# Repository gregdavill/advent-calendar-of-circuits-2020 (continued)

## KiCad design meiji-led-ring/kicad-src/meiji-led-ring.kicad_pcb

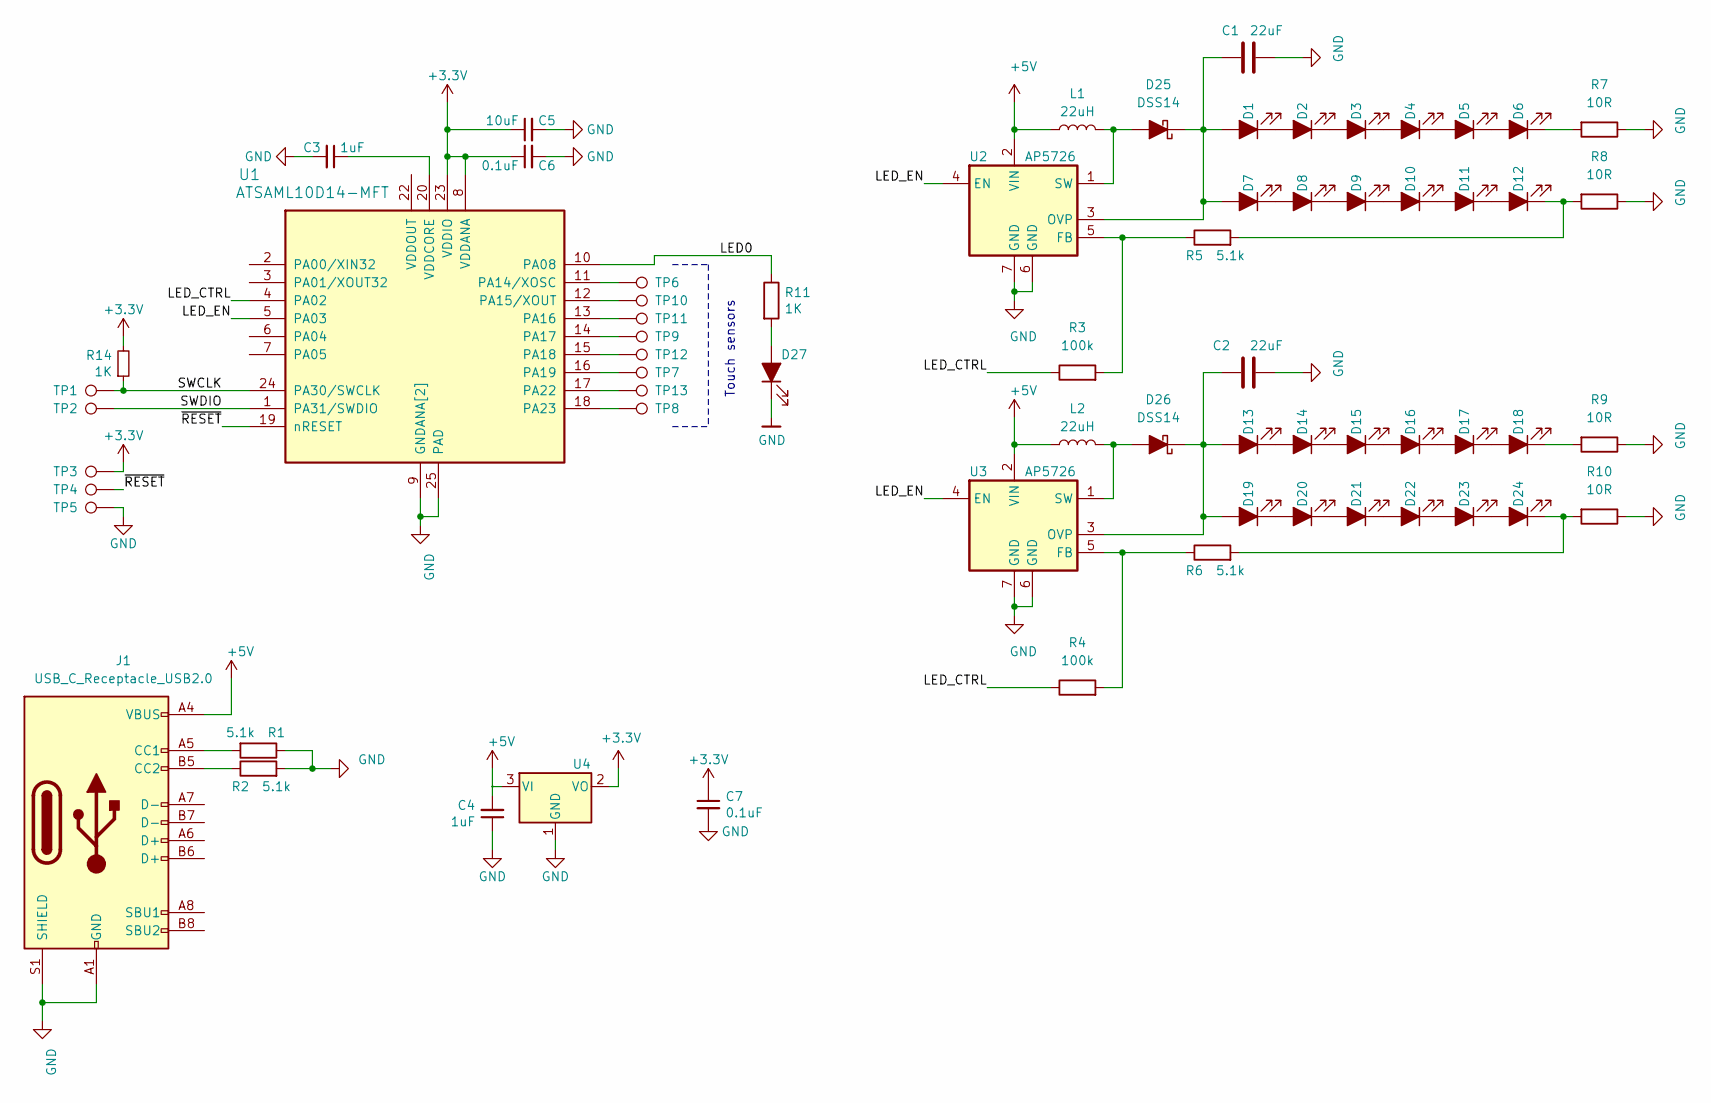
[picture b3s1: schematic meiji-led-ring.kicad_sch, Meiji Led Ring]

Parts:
C1, C2: 22uF; C_1210_3225Metric
C3, C4: 1uF; C_0402_1005Metric
C5: 10uF; C_0402_1005Metric
C6, C7: 0.1uF; C_0402_1005Metric
D1, D2, D3, D4, D5, D6, D7, D8, D9, D10, D11, D12, D13, D14, D15, D16, D17, D18, D19, D20, D21, D22, D23, D24: LED_ALT; LED_LUXEON_3014
D25, D26: DSS14; D_SOD-123F
D27: LED_ALT; LED_0402_1005Metric
J1: USB_C_Receptacle_USB2.0; USB_C_Receptacle_HRO_TYPE-C-31-M-12
L1, L2: 22uH; L_Taiyo-Yuden_NR-40xx
R1, R2, R5, R6: 5.1k; R_0402_1005Metric
R3, R4: 100k; R_0402_1005Metric
R7, R8, R9, R10: 10R; R_0603_1608Metric
R11, R14: 1K; R_0402_1005Metric
TP1: TP_SWCLK; TestPoint_Pad_D1.0mm
TP2: TP_SWDIO; TestPoint_Pad_D1.0mm
TP3: TP_VDD; TestPoint_Pad_D1.0mm
TP4: TP_RESET; TestPoint_Pad_D1.0mm
TP5: TP_GND; TestPoint_Pad_D1.0mm
TP6, TP7, TP8, TP9, TP10, TP11, TP12, TP13: TP_SWCLK; touch_edge_arc
U1: ATSAML10D14-MFT; QFN-24-1EP_5x5mm_P0.65mm_EP3.4x3.4mm
U2, U3: AP5726; DFN-6-1EP_2x2mm_P0.65mm_EP1x1.6mm
U4: MCP1700-3302E_SOT23; SOT-23

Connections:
+3V3: C5.1, C6.1, C7.1, R14.2, TP3.1, U1.8 (VDDANA), U1.23 (VDDIO), U4.2 (VO)
+5V: C4.2, J1.A4 (VBUS), J1.A9 (VBUS), J1.B4 (VBUS), J1.B9 (VBUS), L1.1, L2.1, U2.2 (VIN), U3.2 (VIN), U4.3 (VI)
/LED0: R11.1, U1.10 (PA08)
/LED_CTRL: R3.1, R4.1, U1.4 (PA02)
/LED_EN: U1.5 (PA03), U2.4 (EN), U3.4 (EN)
/SWCLK: R14.1, TP1.1, U1.24 (PA30/SWCLK)
/SWDIO: TP2.1, U1.1 (PA31/SWDIO)
/~RESET~: TP4.1, U1.19 (nRESET)
GND: C1.2, C2.2, C3.2, C4.1, C5.2, C6.2, C7.2, D27.1 (K), J1.A1 (GND), J1.A12 (GND), J1.B1 (GND), J1.B12 (GND), J1.S1 (SHIELD), R1.1, R2.2, R7.1, R8.1, R9.1, R10.1, TP5.1, U1.9 (GNDANA[2]), U1.21 (GNDANA[2]), U1.25 (PAD), U2.6 (GND), U2.7 (GND), U3.6 (GND), U3.7 (GND), U4.1 (GND)
unnamed: C1.1, D1.2 (A), D7.2 (A), D25.1 (K), U2.3 (OVP)
unnamed: C2.1, D13.2 (A), D19.2 (A), D26.1 (K), U3.3 (OVP)
unnamed: C3.1, U1.20 (VDDCORE)
unnamed: D1.1 (K), D2.2 (A)
unnamed: D2.1 (K), D3.2 (A)
unnamed: D3.1 (K), D4.2 (A)
unnamed: D4.1 (K), D5.2 (A)
unnamed: D5.1 (K), D6.2 (A)
unnamed: D6.1 (K), R7.2
unnamed: D7.1 (K), D8.2 (A)
unnamed: D8.1 (K), D9.2 (A)
unnamed: D10.1 (K), D11.2 (A)
unnamed: D9.1 (K), D10.2 (A)
unnamed: D11.1 (K), D12.2 (A)
unnamed: D12.1 (K), R5.2, R8.2
unnamed: D13.1 (K), D14.2 (A)
unnamed: D14.1 (K), D15.2 (A)
unnamed: D15.1 (K), D16.2 (A)
unnamed: D16.1 (K), D17.2 (A)
unnamed: D17.1 (K), D18.2 (A)
unnamed: D18.1 (K), R9.2
unnamed: D19.1 (K), D20.2 (A)
unnamed: D20.1 (K), D21.2 (A)
unnamed: D21.1 (K), D22.2 (A)
unnamed: D22.1 (K), D23.2 (A)
unnamed: D23.1 (K), D24.2 (A)
unnamed: D24.1 (K), R6.2, R10.2
unnamed: D25.2 (A), L1.2, U2.1 (SW)
unnamed: D26.2 (A), L2.2, U3.1 (SW)
unnamed: D27.2 (A), R11.2
unnamed: J1.A5 (CC1), R1.2
unnamed: J1.B5 (CC2), R2.1
unnamed: R3.2, R5.1, U2.5 (FB)
unnamed: R4.2, R6.1, U3.5 (FB)
unnamed: TP6.1, U1.11 (PA14/XOSC)
unnamed: TP7.1, U1.16 (PA19)
unnamed: TP8.1, U1.18 (PA23)
unnamed: TP9.1, U1.14 (PA17)
unnamed: TP10.1, U1.12 (PA15/XOUT)
unnamed: TP11.1, U1.13 (PA16)
unnamed: TP12.1, U1.15 (PA18)
unnamed: TP13.1, U1.17 (PA22)

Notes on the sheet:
Touch sensors

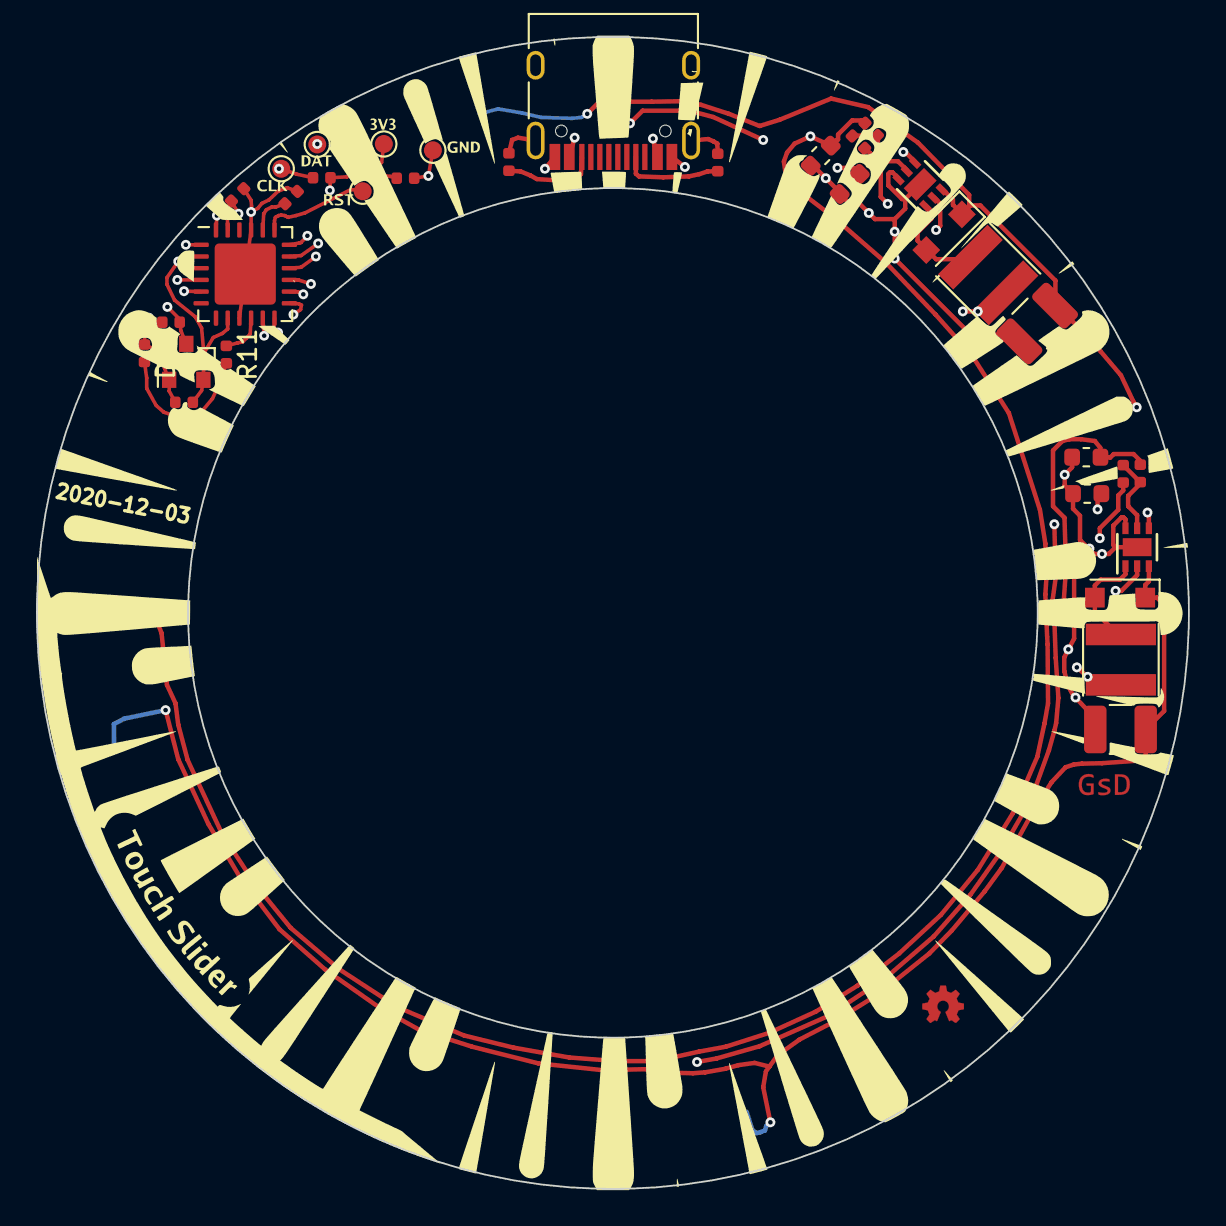
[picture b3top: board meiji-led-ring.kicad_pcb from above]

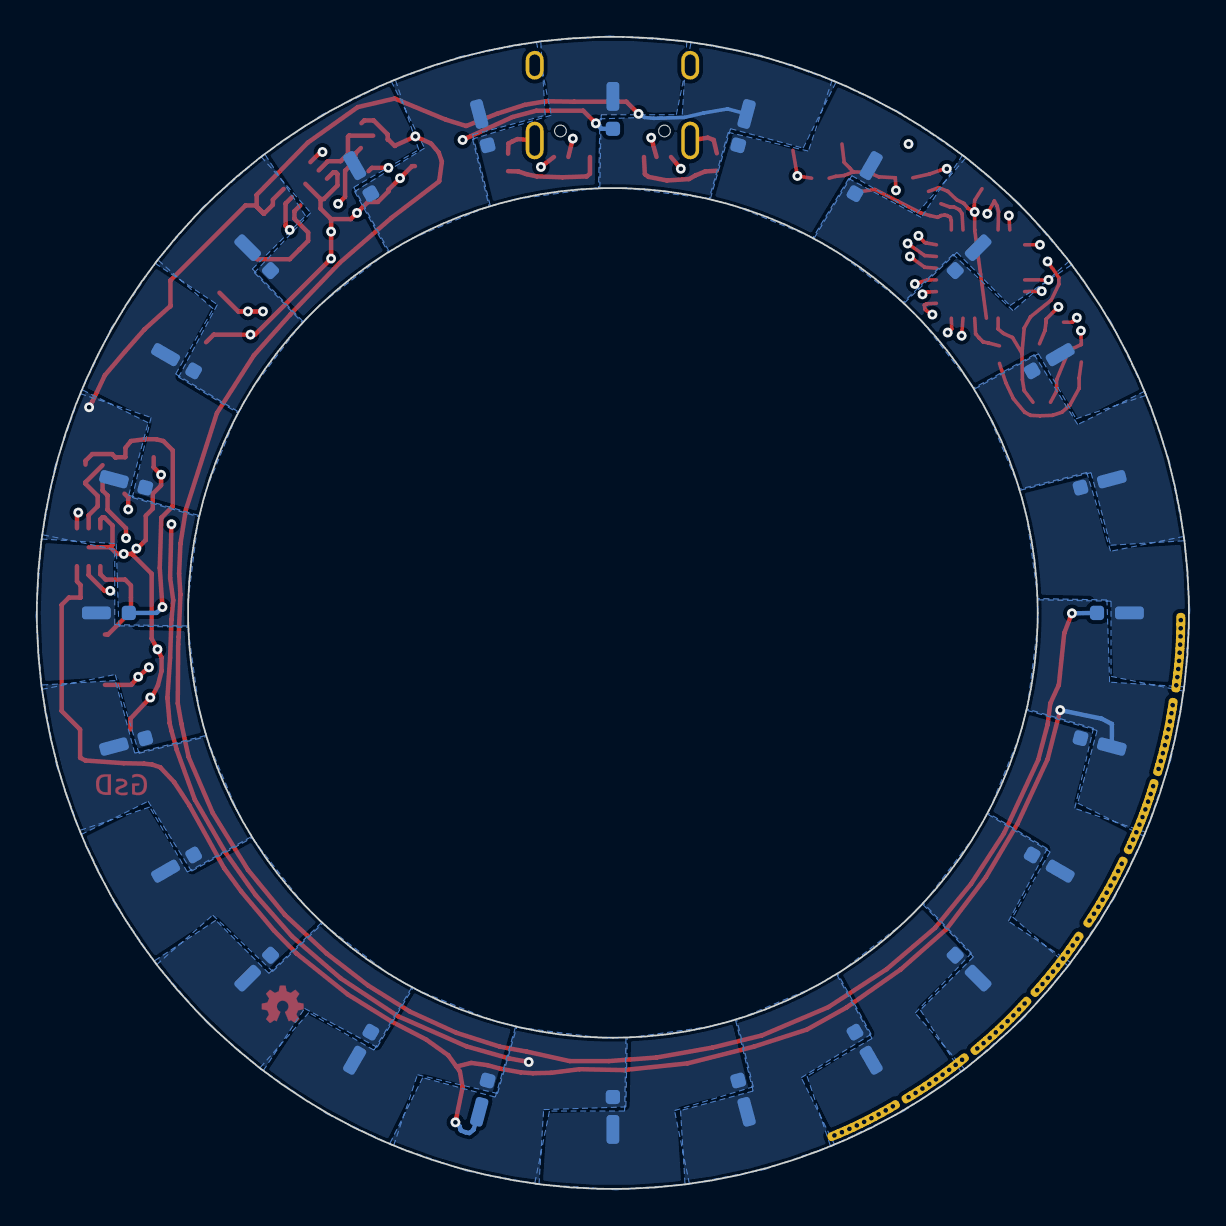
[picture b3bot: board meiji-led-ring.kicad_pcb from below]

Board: 4 copper layers, 64.0 x 64.0 mm, 66 parts (24 on the bottom side), 51 nets.

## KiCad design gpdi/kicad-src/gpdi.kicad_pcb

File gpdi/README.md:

# GPDI breakout

SYZYGY is an FPGA expansion standard for medium to high speed interfaces. Learn more and check out the specifications here: [https://syzygyfpga.io/](https://syzygyfpga.io/)

---

## What is it

A breakout to output video to common digital displays, also supports inputs from digital displays

## Folder structure

```
kicad-src: KiCad v6 source files
production:
 - Gerbers:      [project]_gerbers.zip
 - Schematic:    [project].pdf
 - Board render: [project].png
```

## Render

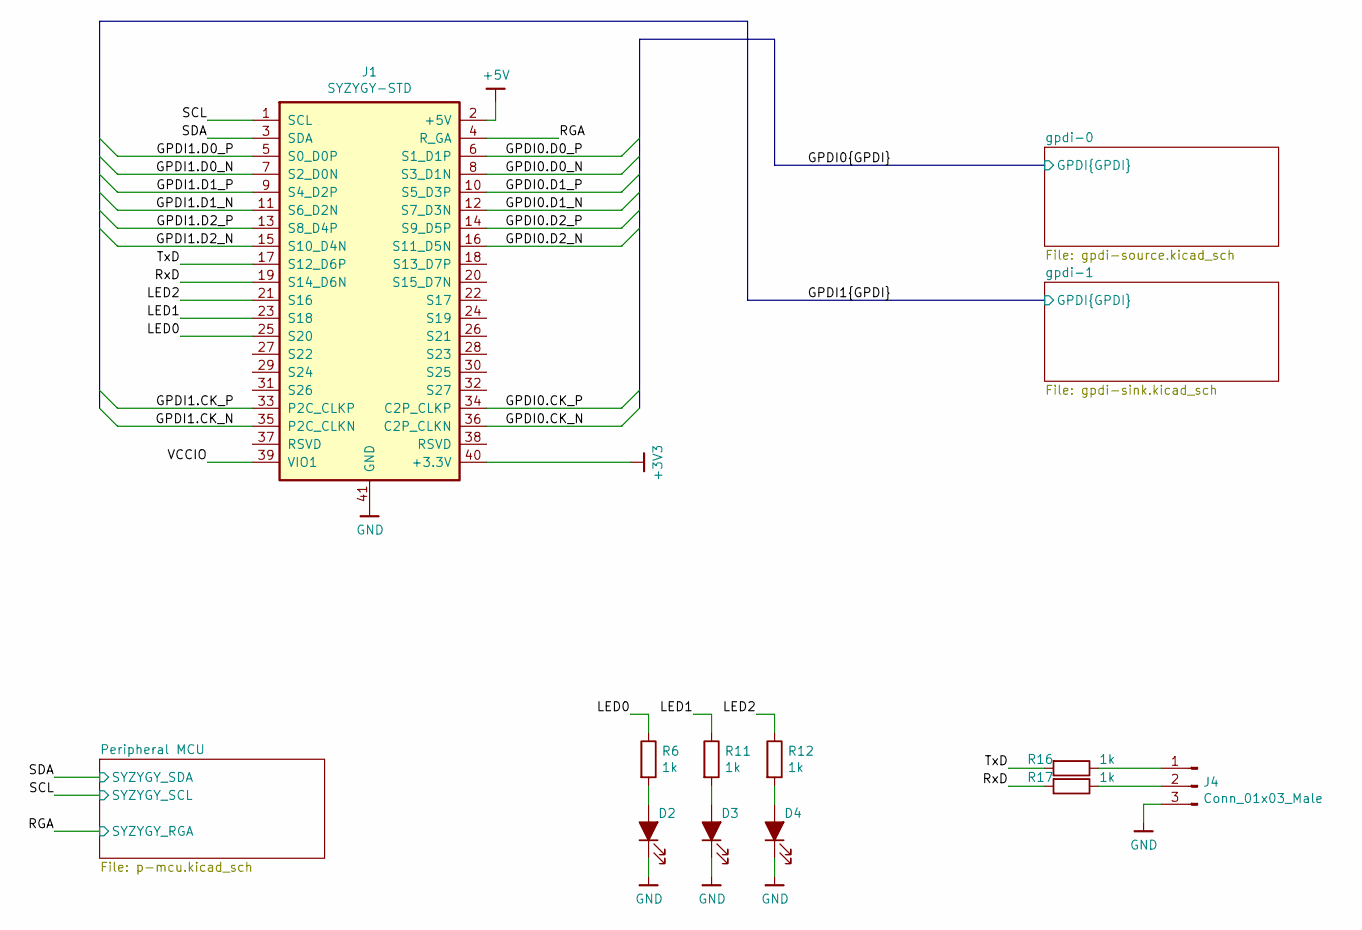
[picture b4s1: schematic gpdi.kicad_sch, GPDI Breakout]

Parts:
D2, D3, D4: LED_ALT; LED_0402_1005Metric
J1: SYZYGY-STD; SYZYGY-STD-POD
J4: Conn_01x03_Male; PinHeader_1x03_P2.54mm_Vertical
R6, R11, R12, R16, R17: 1k; R_0402_1005Metric

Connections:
+3V3: J1.40 (+3.3V); also elsewhere on the board
+5V: J1.2 (+5V); also elsewhere on the board
/GPDI0.CK_N: J1.36 (C2P_CLKN); also elsewhere on the board
/GPDI0.CK_P: J1.34 (C2P_CLKP); also elsewhere on the board
/GPDI0.D0_N: J1.8 (S3_D1N); also elsewhere on the board
/GPDI0.D0_P: J1.6 (S1_D1P); also elsewhere on the board
/GPDI0.D1_N: J1.12 (S7_D3N); also elsewhere on the board
/GPDI0.D1_P: J1.10 (S5_D3P); also elsewhere on the board
/GPDI0.D2_N: J1.16 (S11_D5N); also elsewhere on the board
/GPDI0.D2_P: J1.14 (S9_D5P); also elsewhere on the board
/GPDI1.CK_N: J1.35 (P2C_CLKN); also elsewhere on the board
/GPDI1.CK_P: J1.33 (P2C_CLKP); also elsewhere on the board
/GPDI1.D0_N: J1.7 (S2_D0N); also elsewhere on the board
/GPDI1.D0_P: J1.5 (S0_D0P); also elsewhere on the board
/GPDI1.D1_N: J1.11 (S6_D2N); also elsewhere on the board
/GPDI1.D1_P: J1.9 (S4_D2P); also elsewhere on the board
/GPDI1.D2_N: J1.15 (S10_D4N); also elsewhere on the board
/GPDI1.D2_P: J1.13 (S8_D4P); also elsewhere on the board
/LED0: J1.25 (S20), R6.1
/LED1: J1.23 (S18), R11.1
/LED2: J1.21 (S16), R12.1
/RGA: J1.4 (R_GA); also elsewhere on the board
/RxD: J1.19 (S14_D6N), R17.2
/SCL: J1.1 (SCL); also elsewhere on the board
/SDA: J1.3 (SDA); also elsewhere on the board
/TxD: J1.17 (S12_D6P), R16.2
/VCCIO: J1.39 (VIO1)
GND: D2.1 (K), D3.1 (K), D4.1 (K), J1.41 (GND), J4.3; also elsewhere on the board
unnamed: D2.2 (A), R6.2
unnamed: D3.2 (A), R11.2
unnamed: D4.2 (A), R12.2
unnamed: J4.1, R16.1
unnamed: J4.2, R17.1

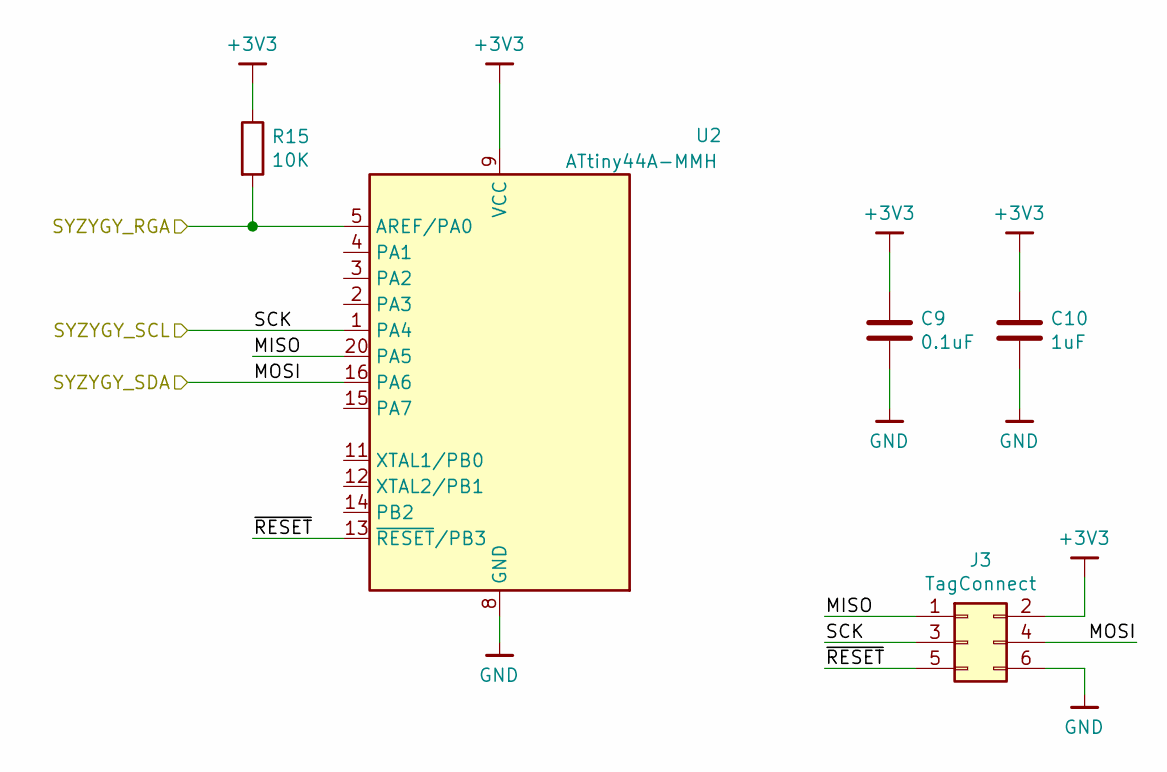
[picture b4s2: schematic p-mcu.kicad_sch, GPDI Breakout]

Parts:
C9: 0.1uF; C_0402_1005Metric
C10: 1uF; C_0402_1005Metric
J3: TagConnect; TC2030-NL_SMALL
R15: 10K; R_0402_1005Metric
U2: ATtiny44A-MMH; QFN-20-1EP_3x3mm_P0.45mm_EP1.6x1.6mm

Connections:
+3V3: C9.1, C10.1, J3.2, R15.1, U2.9 (VCC); also elsewhere on the board
/Peripheral MCU/MISO: J3.1, U2.20 (PA5)
/Peripheral MCU/~RESET: J3.5, U2.13 (~RESET~/PB3)
/RGA: R15.2, U2.5 (AREF/PA0); also elsewhere on the board
/SCL: J3.3, U2.1 (PA4); also elsewhere on the board
/SDA: J3.4, U2.16 (PA6); also elsewhere on the board
GND: C9.2, C10.2, J3.6, U2.8 (GND), U2.21 (GND); also elsewhere on the board

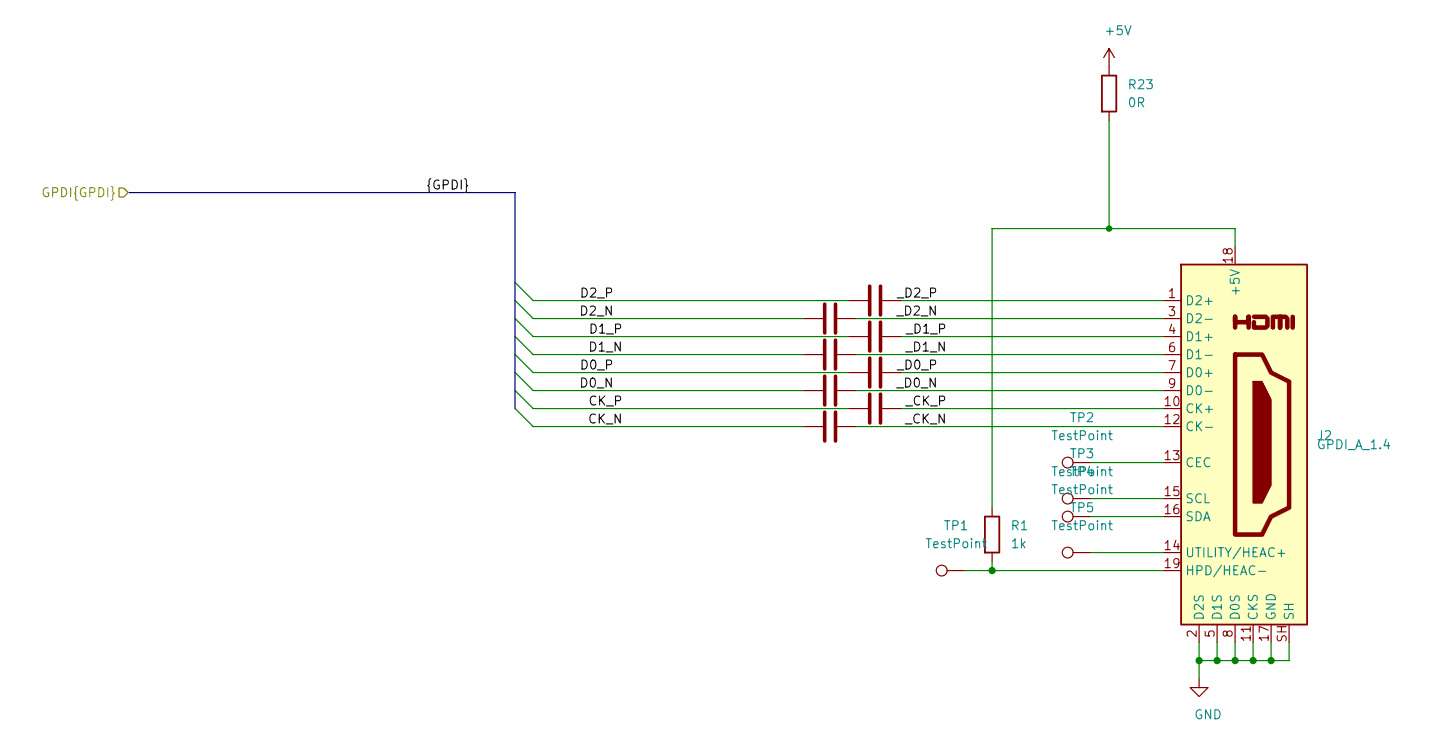
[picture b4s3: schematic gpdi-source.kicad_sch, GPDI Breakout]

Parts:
C1, C2, C3, C4, C5, C6, C7, C8: 0.1uF; C_0402_1005Metric
J2: GPDI_A_1.4; HDMI-10029449-111RLF
R1: 1k; R_0402_1005Metric
R23: 0R; R_0402_1005Metric
TP1, TP2, TP3, TP4, TP5: TestPoint; TestPoint_THTPad_D1.5mm_Drill0.7mm

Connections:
+5V: R23.1; also elsewhere on the board
/GPDI0.CK_N: C4.1; also elsewhere on the board
/GPDI0.CK_P: C8.1; also elsewhere on the board
/GPDI0.D0_N: C3.1; also elsewhere on the board
/GPDI0.D0_P: C7.1; also elsewhere on the board
/GPDI0.D1_N: C2.1; also elsewhere on the board
/GPDI0.D1_P: C6.1; also elsewhere on the board
/GPDI0.D2_N: C1.1; also elsewhere on the board
/GPDI0.D2_P: C5.1; also elsewhere on the board
/gpdi-0/_CK_N: C4.2, J2.12 (CK-)
/gpdi-0/_CK_P: C8.2, J2.10 (CK+)
/gpdi-0/_D0_N: C3.2, J2.9 (D0-)
/gpdi-0/_D0_P: C7.2, J2.7 (D0+)
/gpdi-0/_D1_N: C2.2, J2.6 (D1-)
/gpdi-0/_D1_P: C6.2, J2.4 (D1+)
/gpdi-0/_D2_N: C1.2, J2.3 (D2-)
/gpdi-0/_D2_P: C5.2, J2.1 (D2+)
GND: J2.2 (D2S), J2.5 (D1S), J2.8 (D0S), J2.11 (CKS), J2.17 (GND), J2.SH; also elsewhere on the board
unnamed: J2.13 (CEC), TP2.1
unnamed: J2.14 (UTILITY/HEAC+), TP5.1
unnamed: J2.15 (SCL), TP3.1
unnamed: J2.16 (SDA), TP4.1
unnamed: J2.18 (+5V), R1.1, R23.2
unnamed: J2.19 (HPD/HEAC-), R1.2, TP1.1

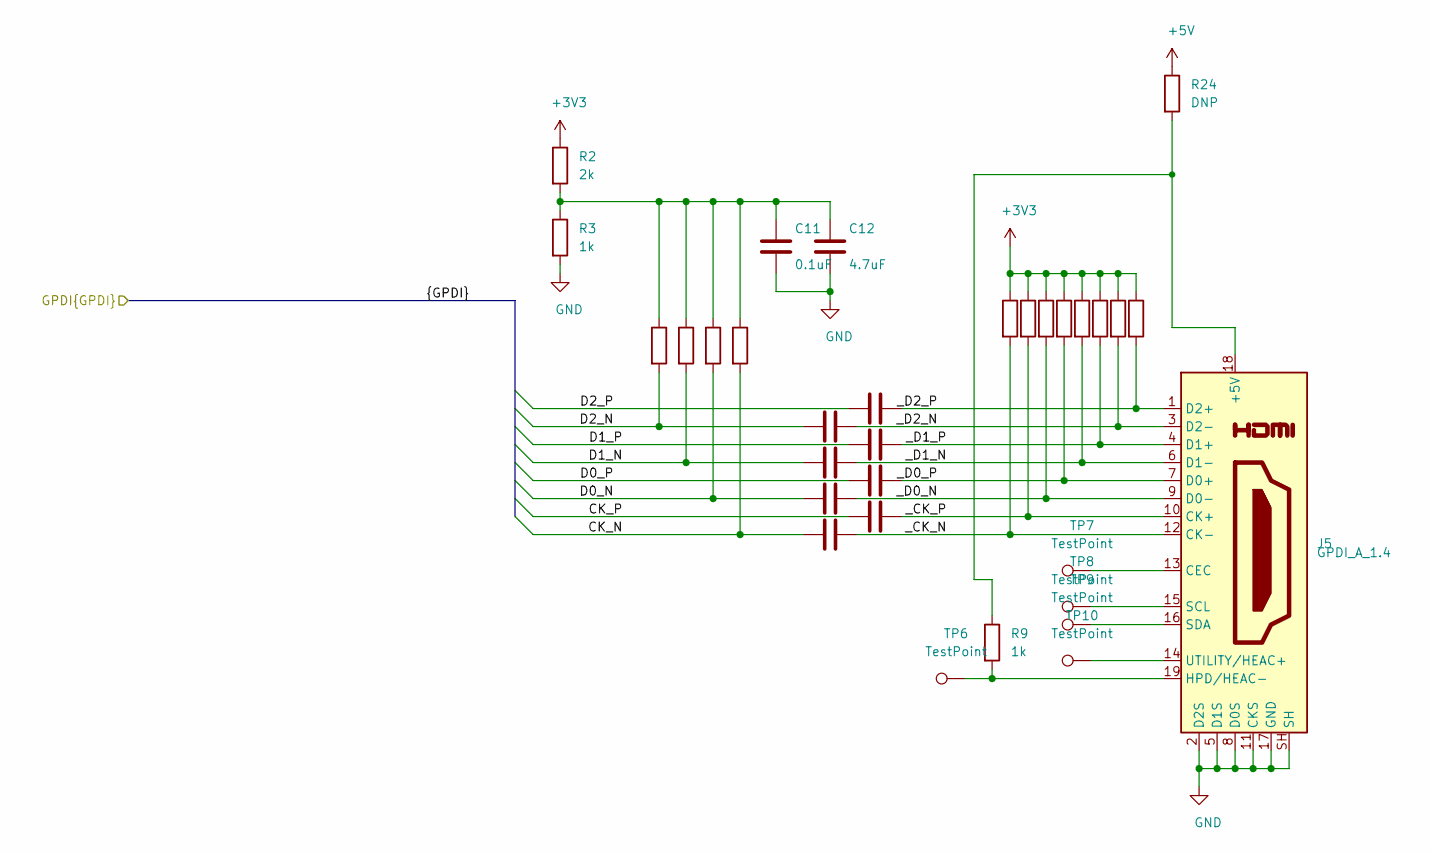
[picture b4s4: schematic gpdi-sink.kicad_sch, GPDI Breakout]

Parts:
C11, C13, C14, C15, C16, C17, C18, C19, C20: 0.1uF; C_0402_1005Metric
C12: 4.7uF; C_0402_1005Metric
J5: GPDI_A_1.4; HDMI-10029449-111RLF
R2: 2k; R_0402_1005Metric
R3, R9: 1k; R_0402_1005Metric
R4, R5, R7, R8: 47k; R_0402_1005Metric
R10, R13, R14, R18, R19, R20, R21, R22: 50R; R_0402_1005Metric
R24: DNP; R_0402_1005Metric
TP6, TP7, TP8, TP9, TP10: TestPoint; TestPoint_THTPad_D1.5mm_Drill0.7mm

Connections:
+3V3: R2.1, R10.1, R13.1, R14.1, R18.1, R19.1, R20.1, R21.1, R22.1; also elsewhere on the board
+5V: R24.1; also elsewhere on the board
/GPDI1.CK_N: C16.1, R8.2; also elsewhere on the board
/GPDI1.CK_P: C20.1; also elsewhere on the board
/GPDI1.D0_N: C15.1, R7.2; also elsewhere on the board
/GPDI1.D0_P: C19.1; also elsewhere on the board
/GPDI1.D1_N: C14.1, R5.2; also elsewhere on the board
/GPDI1.D1_P: C18.1; also elsewhere on the board
/GPDI1.D2_N: C13.1, R4.2; also elsewhere on the board
/GPDI1.D2_P: C17.1; also elsewhere on the board
/gpdi-1/_CK_N: C16.2, J5.12 (CK-), R10.2
/gpdi-1/_CK_P: C20.2, J5.10 (CK+), R13.2
/gpdi-1/_D0_N: C15.2, J5.9 (D0-), R14.2
/gpdi-1/_D0_P: C19.2, J5.7 (D0+), R18.2
/gpdi-1/_D1_N: C14.2, J5.6 (D1-), R19.2
/gpdi-1/_D1_P: C18.2, J5.4 (D1+), R20.2
/gpdi-1/_D2_N: C13.2, J5.3 (D2-), R21.2
/gpdi-1/_D2_P: C17.2, J5.1 (D2+), R22.2
GND: C11.2, C12.2, J5.2 (D2S), J5.5 (D1S), J5.8 (D0S), J5.11 (CKS), J5.17 (GND), J5.SH, R3.2; also elsewhere on the board
unnamed: C11.1, C12.1, R2.2, R3.1, R4.1, R5.1, R7.1, R8.1
unnamed: J5.13 (CEC), TP7.1
unnamed: J5.14 (UTILITY/HEAC+), TP10.1
unnamed: J5.15 (SCL), TP8.1
unnamed: J5.16 (SDA), TP9.1
unnamed: J5.18 (+5V), R9.1, R24.2
unnamed: J5.19 (HPD/HEAC-), R9.2, TP6.1

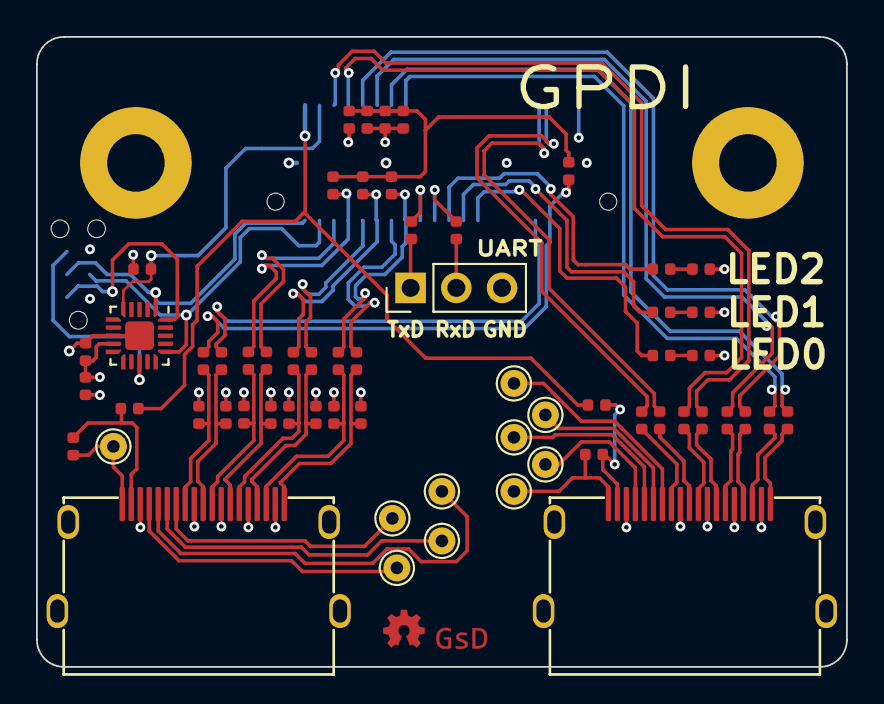
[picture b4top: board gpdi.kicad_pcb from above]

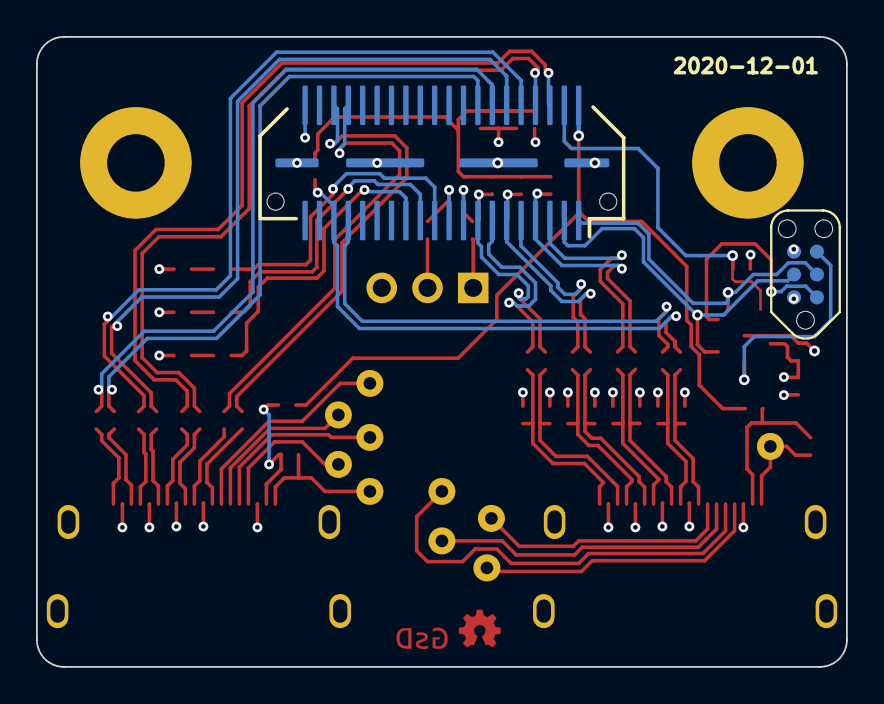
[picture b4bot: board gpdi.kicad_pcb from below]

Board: 4 copper layers, 45.0 x 35.0 mm, 63 parts (2 on the bottom side), 63 nets.

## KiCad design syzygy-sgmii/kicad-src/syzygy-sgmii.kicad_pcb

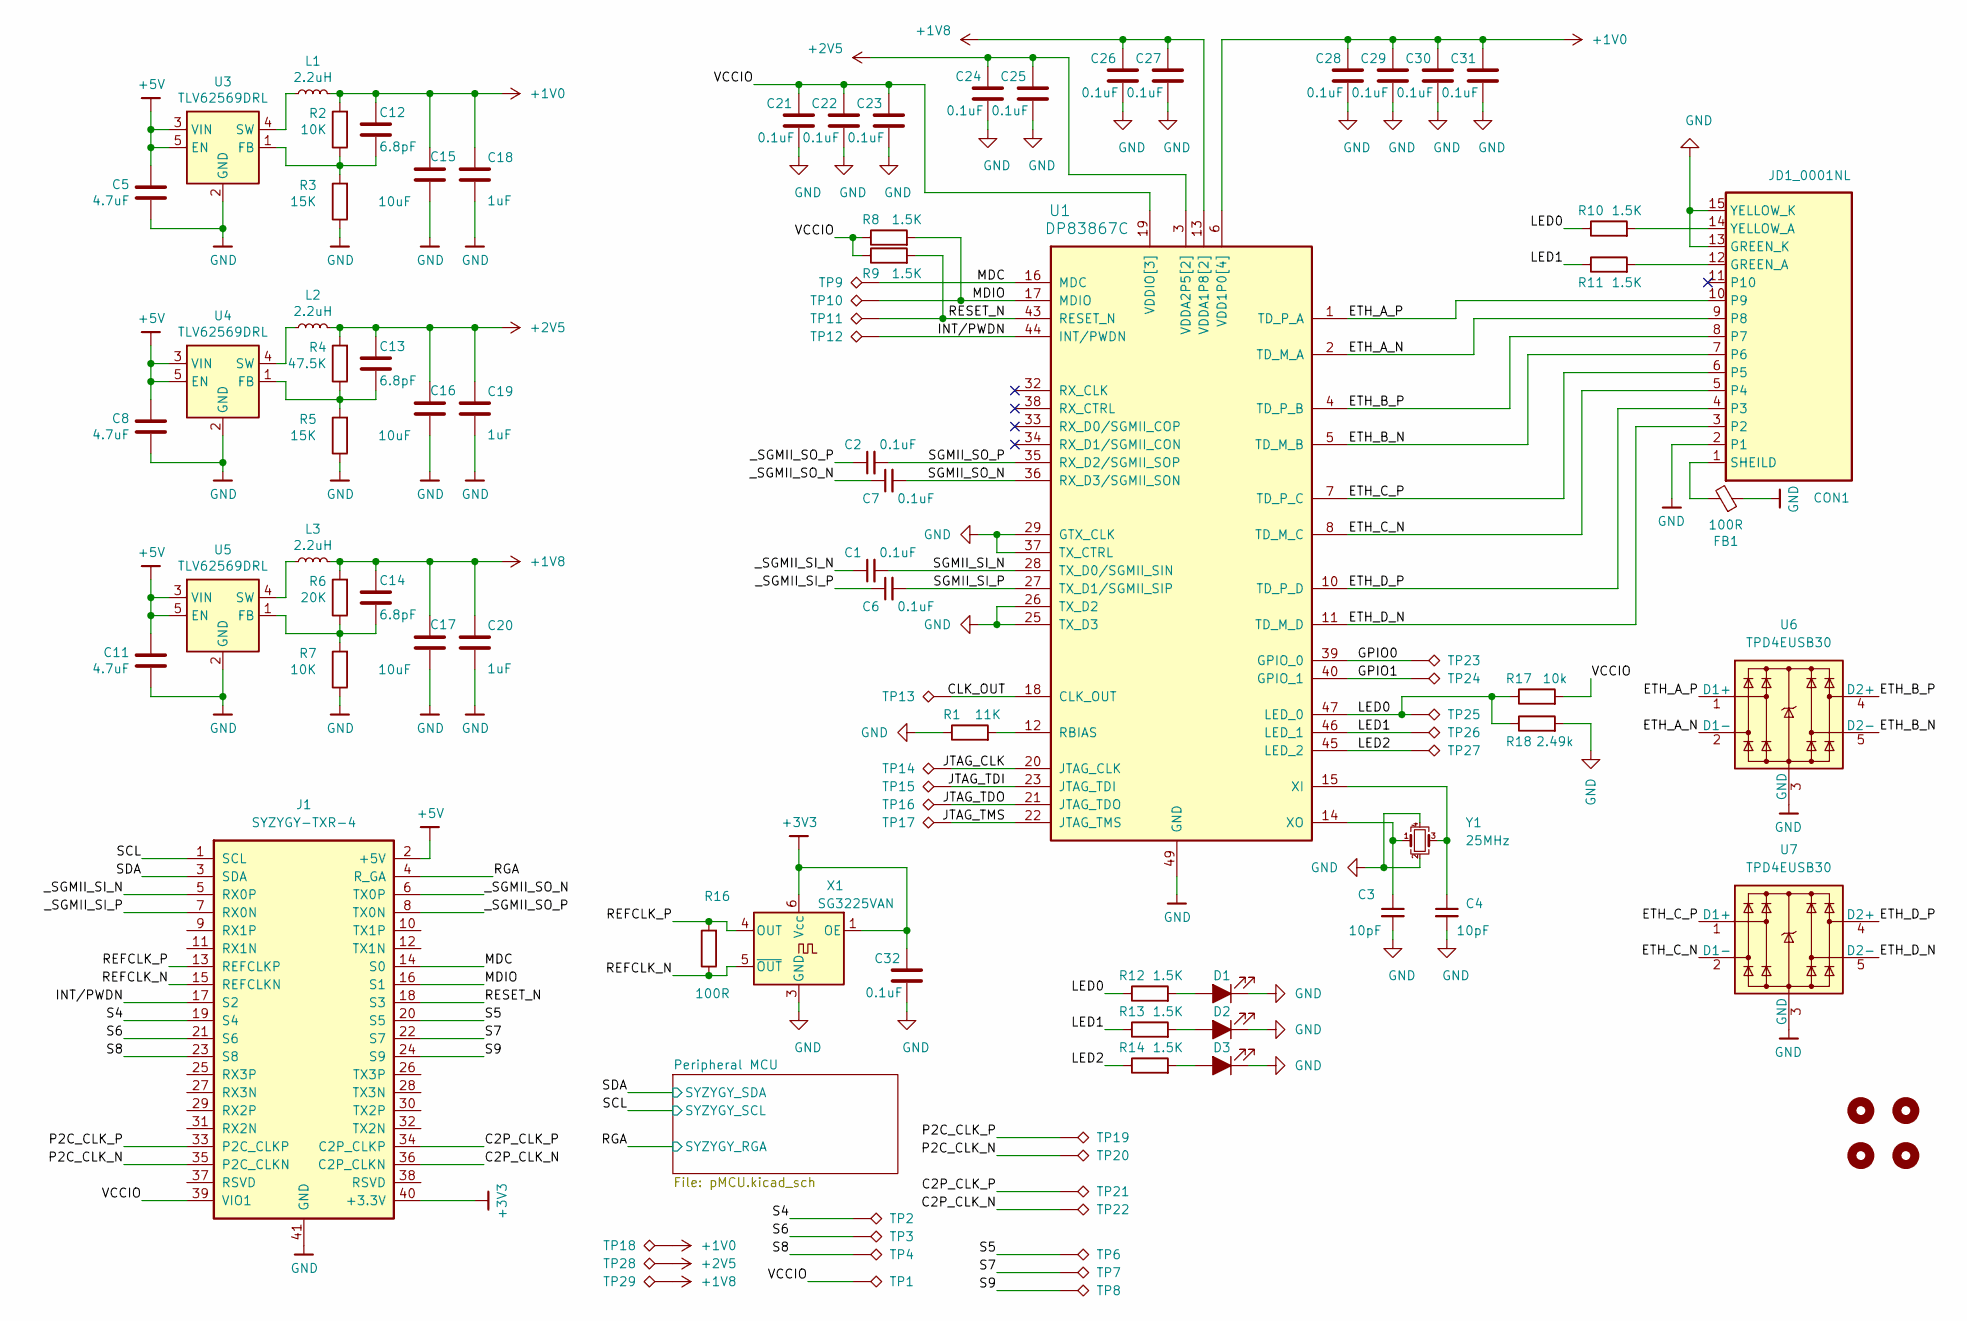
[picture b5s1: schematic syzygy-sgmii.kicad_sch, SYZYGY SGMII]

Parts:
C1, C2, C6, C7, C21, C22, C23, C24, C25, C26, C27, C28, C29, C30, C31, C32: 0.1uF; C_0402_1005Metric
C3, C4: 10pF; C_0402_1005Metric
C5, C8, C11: 4.7uF; C_0402_1005Metric
C12, C13, C14: 6.8pF; C_0402_1005Metric
C15, C16, C17: 10uF; C_0603_1608Metric
C18, C19, C20: 1uF; C_0402_1005Metric
CON1: JD1_0001NL; JD1-0001NL
D1, D2, D3: LED_ALT; LED_0603_1608Metric
FB1: 100R; L_0603_1608Metric
H1, H2, H3, H4: MountingHole; MountingHole_3.2mm_M3
J1: SYZYGY-TXR-4; SYZYGY-TXR-POD
L1, L2, L3: 2.2uH; L_0805_2012Metric
R1: 11K; R_0402_1005Metric
R2, R7: 10K; R_0402_1005Metric
R3, R5: 15K; R_0402_1005Metric
R4: 47.5K; R_0402_1005Metric
R6: 20K; R_0402_1005Metric
R8, R9, R10, R11, R12, R13, R14: 1.5K; R_0402_1005Metric
R16: 100R; R_0402_1005Metric
R17: 10k; R_0402_1005Metric
R18: 2.49k; R_0402_1005Metric
TP1, TP2, TP3, TP4, TP6, TP7, TP8, TP9, TP10, TP11, TP12, TP13, TP14, TP15, TP16, TP17, TP18, TP19, TP20, TP21, TP22, TP23, TP24, TP25, TP26, TP27, TP28, TP29: TestPoint_Alt; TestPoint_Pad_D1.0mm
U1: DP83867C; QFN-48-1EP_7x7mm_P0.5mm_EP5.15x5.15mm_ThermalVias
U3, U4, U5: TLV62569DRL; SOT-666
U6, U7: TPD4EUSB30; USON-10_2.5x1.0mm_P0.5mm
X1: SG3225VAN; Oscillator_SMD_Silicon_Labs_LGA-6_2.5x3.2mm_P1.25mm
Y1: 25MHz; Crystal_SMD_SeikoEpson_TSX3225-4Pin_3.2x2.5mm

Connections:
+1V0: C12.1, C15.1, C18.1, C28.1, C29.1, C30.1, C31.1, L1.2, R2.2, TP18.1, U1.6 (VDD1P0[4]), U1.24 (VDD1P0[4]), U1.31 (VDD1P0[4]), U1.42 (VDD1P0[4])
+1V8: C14.1, C17.1, C20.1, C26.1, C27.1, L3.2, R6.2, TP29.1, U1.13 (VDDA1P8[2]), U1.48 (VDDA1P8[2])
+2V5: C13.1, C16.1, C19.1, C24.1, C25.1, L2.2, R4.2, TP28.1, U1.3 (VDDA2P5[2]), U1.9 (VDDA2P5[2])
+3V3: C32.1, J1.40 (+3.3V), X1.1 (OE), X1.6 (Vcc); also elsewhere on the board
+5V: C5.1, C8.1, C11.1, J1.2 (+5V), U3.3 (VIN), U3.5 (EN), U4.3 (VIN), U4.5 (EN), U5.3 (VIN), U5.5 (EN)
/C2P_CLK_N: J1.36 (C2P_CLKN), TP22.1
/C2P_CLK_P: J1.34 (C2P_CLKP), TP21.1
/CLK_OUT: TP13.1, U1.18 (CLK_OUT)
/ETH_A_N: CON1.9 (P8), U1.2 (TD_M_A), U6.2 (D1-)
/ETH_A_P: CON1.10 (P9), U1.1 (TD_P_A), U6.1 (D1+)
/ETH_B_N: CON1.7 (P6), U1.5 (TD_M_B), U6.5 (D2-)
/ETH_B_P: CON1.8 (P7), U1.4 (TD_P_B), U6.4 (D2+)
/ETH_C_N: CON1.5 (P4), U1.8 (TD_M_C), U7.2 (D1-)
/ETH_C_P: CON1.6 (P5), U1.7 (TD_P_C), U7.1 (D1+)
/ETH_D_N: CON1.3 (P2), U1.11 (TD_M_D), U7.5 (D2-)
/ETH_D_P: CON1.4 (P3), U1.10 (TD_P_D), U7.4 (D2+)
/GPIO0: TP23.1, U1.39 (GPIO_0)
/GPIO1: TP24.1, U1.40 (GPIO_1)
/INT/PWDN: J1.17 (S2), TP12.1, U1.44 (INT/PWDN)
/JTAG_CLK: TP14.1, U1.20 (JTAG_CLK)
/JTAG_TDI: TP15.1, U1.23 (JTAG_TDI)
/JTAG_TDO: TP16.1, U1.21 (JTAG_TDO)
/JTAG_TMS: TP17.1, U1.22 (JTAG_TMS)
/LED0: R10.1, R12.1, R17.1, R18.1, TP25.1, U1.47 (LED_0)
/LED1: R11.1, R13.1, TP26.1, U1.46 (LED_1)
/LED2: R14.1, TP27.1, U1.45 (LED_2)
/MDC: J1.14 (S0), TP9.1, U1.16 (MDC)
/MDIO: J1.16 (S1), R8.2, TP10.1, U1.17 (MDIO)
/P2C_CLK_N: J1.35 (P2C_CLKN), TP20.1
/P2C_CLK_P: J1.33 (P2C_CLKP), TP19.1
/REFCLK_N: J1.15 (REFCLKN), R16.1, X1.5 (~OUT)
/REFCLK_P: J1.13 (REFCLKP), R16.2, X1.4 (OUT)
/RESET_N: J1.18 (S3), R9.2, TP11.1, U1.43 (RESET_N)
/RGA: J1.4 (R_GA); also elsewhere on the board
/S4: J1.19 (S4), TP2.1
/S5: J1.20 (S5), TP6.1
/S6: J1.21 (S6), TP3.1
/S7: J1.22 (S7), TP7.1
/S8: J1.23 (S8), TP4.1
/S9: J1.24 (S9), TP8.1
/SCL: J1.1 (SCL); also elsewhere on the board
/SDA: J1.3 (SDA); also elsewhere on the board
/SGMII_SI_N: C1.2, U1.28 (TX_D0/SGMII_SIN)
/SGMII_SI_P: C6.2, U1.27 (TX_D1/SGMII_SIP)
/SGMII_SO_N: C7.2, U1.36 (RX_D3/SGMII_SON)
/SGMII_SO_P: C2.2, U1.35 (RX_D2/SGMII_SOP)
/VCCIO: C21.1, C22.1, C23.1, J1.39 (VIO1), R8.1, R9.1, R17.2, TP1.1, U1.19 (VDDIO[3]), U1.30 (VDDIO[3]), U1.41 (VDDIO[3])
/_SGMII_SI_N: C1.1, J1.5 (RX0P)
/_SGMII_SI_P: C6.1, J1.7 (RX0N)
/_SGMII_SO_N: C7.1, J1.6 (TX0P)
/_SGMII_SO_P: C2.1, J1.8 (TX0N)
GND: C3.2, C4.2, C5.2, C8.2, C11.2, C15.2, C16.2, C17.2, C18.2, C19.2, C20.2, C21.2, C22.2, C23.2, C24.2, C25.2, C26.2, C27.2, C28.2, C29.2, C30.2, C31.2, C32.2, CON1.2 (P1), CON1.13 (GREEN_K), CON1.15 (YELLOW_K), D1.1 (K), D2.1 (K), D3.1 (K), FB1.1, J1.41 (GND), R1.1, R3.1, R5.1, R7.1, R18.2, U1.25 (TX_D3), U1.26 (TX_D2), U1.29 (GTX_CLK), U1.37 (TX_CTRL), U1.49 (GND), U3.2 (GND), U4.2 (GND), U5.2 (GND), U6.3 (GND), U6.8 (GND), U7.3 (GND), U7.8 (GND), X1.3 (GND), Y1.2, Y1.4; also elsewhere on the board
unnamed: C3.1, U1.14 (XO), Y1.1
unnamed: C4.1, U1.15 (XI), Y1.3
unnamed: C12.2, R2.1, R3.2, U3.1 (FB)
unnamed: C13.2, R4.1, R5.2, U4.1 (FB)
unnamed: C14.2, R6.1, R7.2, U5.1 (FB)
unnamed: CON1.1 (SHEILD), FB1.2
unnamed: CON1.12 (GREEN_A), R11.2
unnamed: CON1.14 (YELLOW_A), R10.2
unnamed: D1.2 (A), R12.2
unnamed: D2.2 (A), R13.2
unnamed: D3.2 (A), R14.2
unnamed: L1.1, U3.4 (SW)
unnamed: L2.1, U4.4 (SW)
unnamed: L3.1, U5.4 (SW)
unnamed: R1.2, U1.12 (RBIAS)

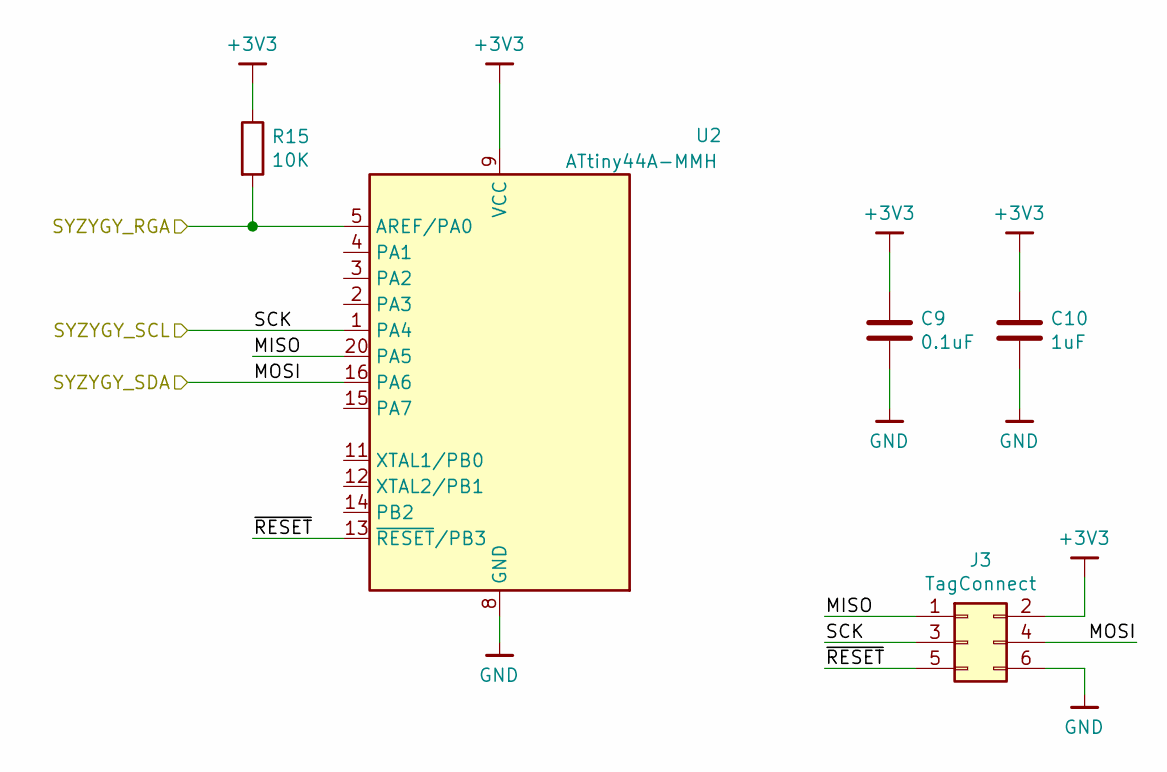
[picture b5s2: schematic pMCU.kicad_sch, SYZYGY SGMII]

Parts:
C9: 0.1uF; C_0402_1005Metric
C10: 1uF; C_0402_1005Metric
J3: TagConnect; TC2030-NL_SMALL
R15: 10K; R_0402_1005Metric
U2: ATtiny44A-MMH; QFN-20-1EP_3x3mm_P0.45mm_EP1.6x1.6mm

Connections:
+3V3: C9.1, C10.1, J3.2, R15.1, U2.9 (VCC); also elsewhere on the board
/Peripheral MCU/MISO: J3.1, U2.20 (PA5)
/Peripheral MCU/~RESET: J3.5, U2.13 (~RESET~/PB3)
/RGA: R15.2, U2.5 (AREF/PA0); also elsewhere on the board
/SCL: J3.3, U2.1 (PA4); also elsewhere on the board
/SDA: J3.4, U2.16 (PA6); also elsewhere on the board
GND: C9.2, C10.2, J3.6, U2.8 (GND), U2.21 (GND); also elsewhere on the board
